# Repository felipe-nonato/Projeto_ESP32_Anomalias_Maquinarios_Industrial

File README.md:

# Projeto_ESP32_Anomalias_Maquinarios_Industrial

Sistema completo de detecção de anomalias em maquinários industriais com solução embarcada (ESP32 + INMP441), modelo de Machine Learning (Edge Impulse) e dashboard web com mapa interativo para monitoramento em tempo real.

Este repositório contém principalmente a parte do front‑end (dashboard e mapas), enquanto a proposta e a implementação do protótipo embarcado estão em:

## Visão geral do sistema (end‑to‑end)

- Dispositivo embarcado (ESP32):
  - Captura áudio com microfone I2S INMP441.
  - Armazena gravações em microSD.
  - Executa inferência local usando o modelo exportado pelo Edge Impulse (biblioteca C++).
  - Mostra status no display LCD I2C e permite iniciar gravação por botão físico.

- Machine Learning:
  - Treinamento com MIMII Dataset (válvulas solenoides) usando MFCC + rede neural.
  - Exportação do modelo quantizado (int8) e integração ao firmware do ESP32 via Edge Impulse.
  - Processo: extração de MFCC → inferência → probabilidade "normal" vs "anomalia".

- Backend / Telemetria:
  - O ESP32 pode enviar eventos (MQTT / HTTP / WebSocket) com payload JSON (ver seção Formato de Dados).
  - Eventos incluem localização, leituras de sensores e resultado da inferência.

- Front‑end (dashboard + mapa):
  - Recebe e exibe telemetria em tempo real.
  - Lista de máquinas, gráficos temporais, KPIs, painel de alertas.
  - Mapa interativo (Leaflet ou Google Maps) com marcadores coloridos por severidade e clustering.

## Hardware (resumo)

- ESP32‑WROOM (microcontrolador)
- Microfone INMP441 (I2S)
- Módulo microSD (SPI)
- Display LCD 16x2 I2C
- Botão físico para iniciar gravação
- Opcional: case/PCB para integração final

## Formato de dados (payload esperado)

Exemplo de payload JSON enviado ao dashboard / broker:

{
  "device_id": "maquina-01",
  "timestamp": "2025-12-03T12:34:56Z",
  "location": { "lat": -23.55052, "lng": -46.633308 },
  "sensors": { "vibration": 0.12, "temperature": 68.4, "current": 2.3 },
  "anomaly": { "detected": true, "score": 0.86, "severity": "high", "type": "bearing" }
}

(O mesmo formato está referenciado no dashboard deste repositório.)

## Como funciona a inferência embarcada (resumo técnico)

1. Captura de áudio por 10 s (configurável).
2. Pré‑processamento: normalização e extração de MFCCs (compatível com o pipeline do Edge Impulse).
3. Inferência com modelo quantizado (biblioteca C++ gerada pelo Edge Impulse).
4. Resultado: score de anomalia + classificação → exibido no LCD e enviado ao backend.

Benefícios: baixa latência, privacidade (áudio não enviado), operação off‑line.

## Instalação e execução (rápido)

- Firmware (ESP32):
  - Importar a biblioteca gerada pelo Edge Impulse (arquivo .h/.cpp) para o projeto Arduino/PlatformIO.
  - Configurar pinos I2S, SPI (microSD) e I2C (LCD) conforme o esquema de montagem.
  - Compilar e gravar no ESP32 com Arduino IDE ou PlatformIO.

- Dashboard (front‑end):
  - Recomendado: Node.js + framework (React / Vue).
  - Instalar dependências:
    ```sh
    npm install
    npm run dev
    ```
  - Configurar conexão a broker MQTT / WebSocket ou endpoint HTTP que receberá os payloads do ESP32.

## Mapa e visualização

- Implementar com Leaflet (react‑leaflet) ou Google Maps.
- Marcadores codificados por severidade: verde/amarelo/vermelho.
- Popups com link para painel da máquina e histórico.
- Usar marker clustering quando houver muitos dispositivos.

## Desenvolvimento e testes

- Testar parsers de payload (unit tests).
- Simular eventos via MQTT/WS para validar atualização do mapa e KPIs.
- Validar pipeline completo: gravação → inferência local → envio → dashboard.

## Boas práticas e limitações

- Validar e sanitizar todos os payloads antes de renderizar.
- Debounce / rate limit de atualizações do mapa para preservar performance.
- Design do modelo balanceado para reduzir falsos negativos em anomalias raras.
- Limitações: o treinamento não é feito no ESP32; sensores adicionais (vibração/temperatura) não estão incluídos no escopo inicial.

## Referências e documentos do projeto

- MIMII Dataset — referência usada no treinamento (ver proposta).

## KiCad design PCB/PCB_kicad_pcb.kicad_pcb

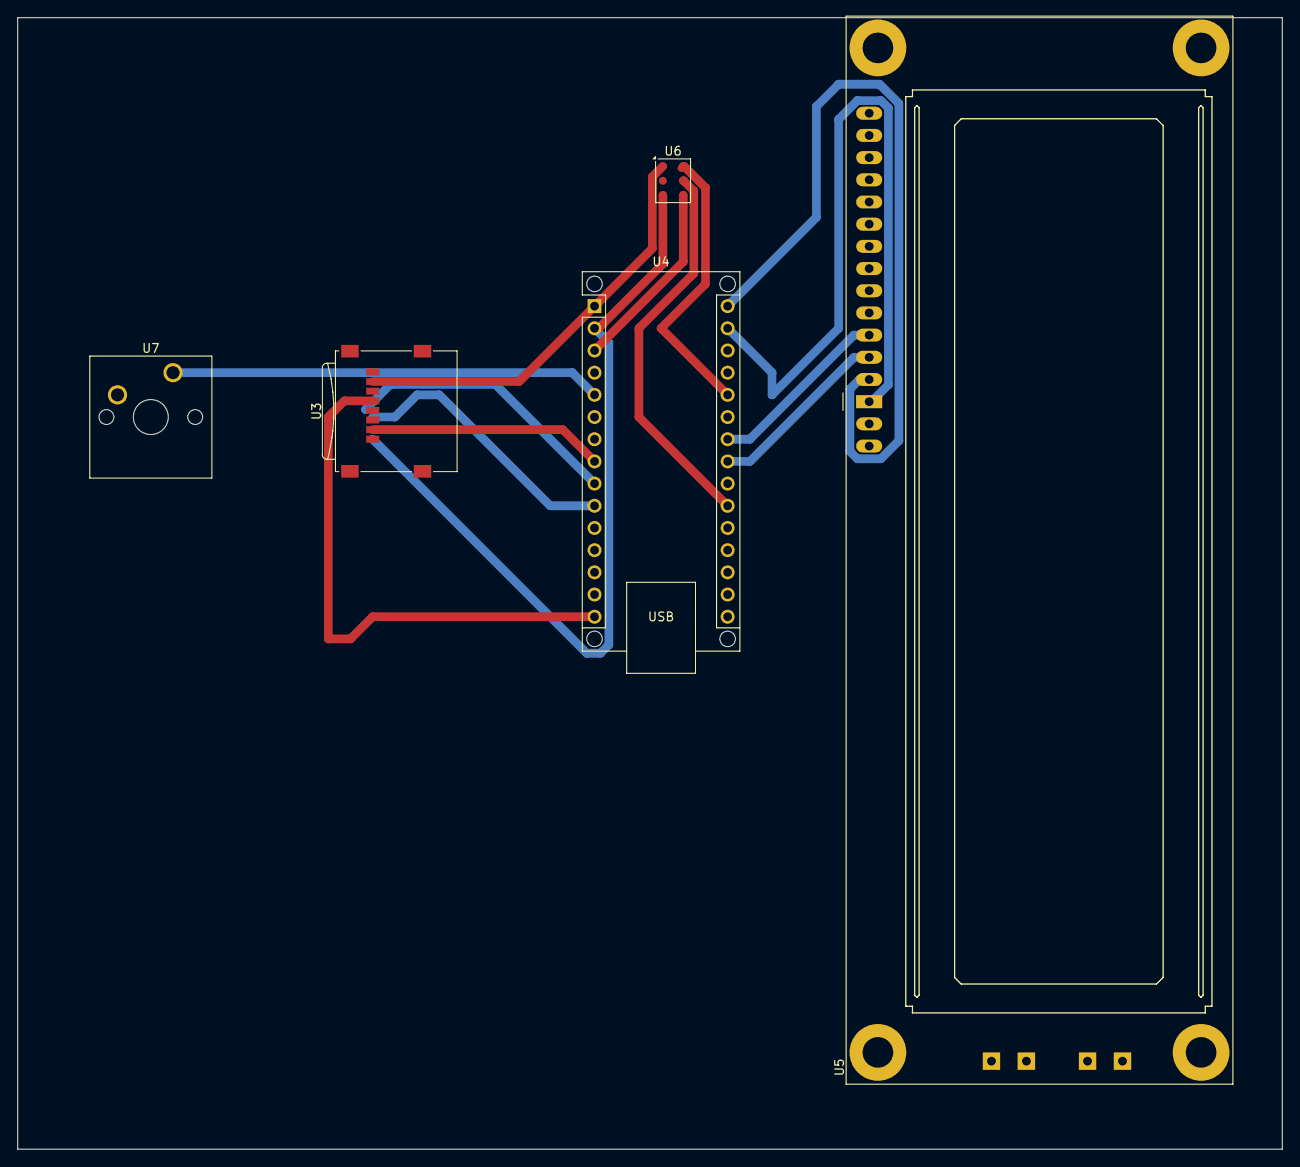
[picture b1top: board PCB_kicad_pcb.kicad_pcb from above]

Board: 2 copper layers, 144.8 x 129.5 mm, 5 parts (0 on the bottom side), 14 nets.

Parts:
U3: SD CARD MODULE; microSD_HC_Wuerth_693072010801
U4: ESP-WROOM-32; Arduino_Nano_WithMountingHoles
U5: Display LCD1602 I2C; LCD-016N002L
U6: INMP441_KP; ST_HLGA-6_3.76x4.72mm_P1.65mm
U7: TL6190BUTTON; SW_Cherry_MX_1.00u_PCB

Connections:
unnamed: U3.7 (+3.3V), U4.1 (3V3), U6.1 (VDD)
unnamed: U3.2 (CS), U4.8 (D5)
unnamed: U3.4 (MISO), U4.10 (D19)
unnamed: U3.5 (MOSI), U4.15 (D23)
unnamed: U3.3 (SCK), U4.9 (D18)
unnamed: U4.5 (D4), U7.1
unnamed: U4.26 (D14), U6.6 (SCK)
unnamed: U4.3 (D15), U6.4 (WS)
unnamed: U4.23 (D25), U5.3 (SCL)
unnamed: U4.24 (D26), U5.4 (SDA)
unnamed: U4.21 (D32), U6.5 (SD)
unnamed: U4.30 (VIN), U5.2 (+5V)
unnamed: U4.29 (GND), U5.1 (GND)
unnamed: U3.1 (Gnd), U4.2 (GND), U6.2 (GND), U6.3 (L/R)

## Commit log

2025-12-03 adicionando readme temporario
2025-12-03 chore(frontend): Criação da estrutura do projeto frontend
2025-12-03 Create README.md for MQTT definitions and usage
    Added detailed MQTT documentation including topics, payload structure, and examples.
2025-12-06 configs
2025-12-06 Add main functionality for ESP32 audio inference project
    This commit adds the main functionality for an ESP32 project that connects to WiFi, records audio to an SD card, and performs inference using a machine learning model. It includes setup for I2S, MQTT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
2025-12-06 feat(dashboard): Adição de icones e configuração mqtt
2025-12-06 external mqtt
2025-12-06 Rename main.c to main.ino
2025-12-06 feat(comunicação): Ligação de broker com frontend
2025-12-08 feat(frontend): device-manager
2025-12-08 fix: ajustes de tipagem e configurações
2025-12-08 feat: integração completa com banco de dados SQLite via API
2025-12-23 Remove hardcoded WiFi and MQTT server credentials
    Clear WiFi and MQTT server credentials for security.
